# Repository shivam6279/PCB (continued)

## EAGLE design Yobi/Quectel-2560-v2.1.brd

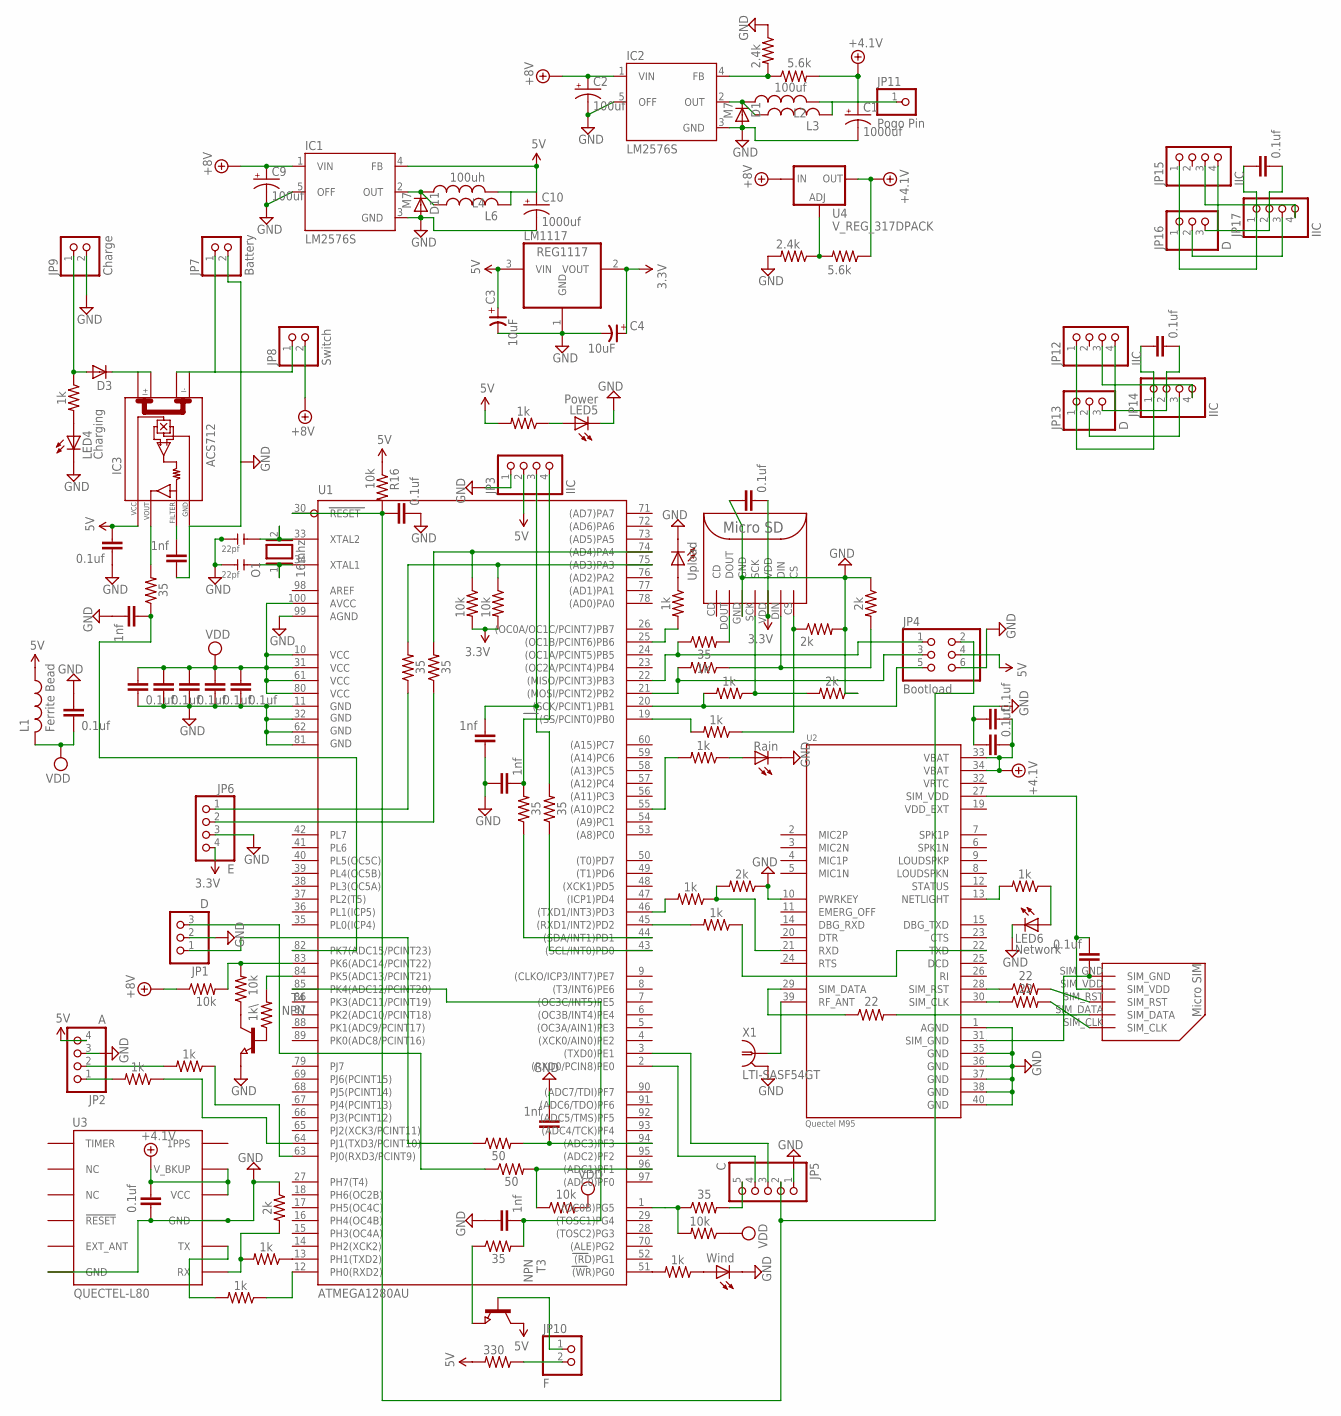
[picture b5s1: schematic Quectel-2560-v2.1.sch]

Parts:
C1, C10: 1000uf; 153CLV-1012
C2, C9: 100uf; CT7343
C3, C4: 10uF; 3528/T
C7, C8: 22pf; C0805
D1, D11: M7; SOD106A
D3: BYS10; SOD106A
DC1, DC2, DC3, DC4, DC5, DC6, DC7, DC8, DC9, DC10, DC11, DC15, DC16, DC18, DC19: 0.1uf; C0805
DC12, DC13, DC14, DC17, DC20, DC21: 1nf; C0805
IC1, IC2: LM2576S; TO263-5
IC3: ACS712; SO08
JP1, JP13, JP16: D; 1X03
JP2: A; 1X04
JP3, JP12, JP14, JP15, JP17: IIC; 1X04
JP4: Bootload; 2X03
JP5: C; 1X05
JP6: E; 1X04
JP7: Battery; 1X02
JP8: Switch; 1X02
JP9: Charge; 1X02
JP10: F; 1X02
JP11: Pogo Pin; 1X01
L1: Ferrite Bead; L2012C
L2: 100uf; PIS2816
L3, L6: L-US6000-XXX-RC; 6000-XXXX-RC
L4: 100uh; PIS2816
LED1: Rain; CHIP-LED0805
LED2: Upload; CHIP-LED0805
LED3: Wind; CHIP-LED0805
LED4: Charging; CHIP-LED0805
LED5: Power; CHIP-LED0805
LED6: Network; CHIP-LED0805
LM1117: REG1117; SOT223
O1: 16mhz; QS
R1, R5, R19, R22, R30, R35, R39, R42: 35; 0805
R4, R9, R23, R24, R29: 2k; 0805
R6, R7, R8, R12, R13, R14, R15, R17, R18, R25, R26, R27, R28, R32, R33: 1k; 0805
R10, R11, R47: 22; 0805
R16, R20, R34, R36, R40, R43, R44: 10k; 0805
R21, R31: 50; 0805
R41: 330; 0805
R45, R49: 2.4k; 0805
R46, R50: 5.6k; 0805
R48: 1k\; 0805
T3, T4: NPN; SOT23
U1: ATMEGA1280AU; TQFP100
U2: Quectel M95; XCVR_M95
U3: QUECTEL-L80
U4: V_REG_317DPACK; V-REG_DPACK
U$1: MICROSD
U$2: MICROSIM
X1: LTI-SASF54GT

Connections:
3.3V: C4.+, DC10.2, JP6.4, LM1117.2 (VOUT), R34.2, R36.2, U$1.VDD
5V: C3.+, C10.+, DC19.2, IC1.4 (FB), IC3.8 (VCC), JP2.4, JP3.2, JP4.4, L1.1, L4.2, L6.2, LM1117.3 (VIN), R16.1, R18.2, R41.2, T3.3 (C)
+4.1V: C1.+, DC6.2, DC7.2, DC16.1, JP11.1, L2.2, L3.2, R46.2, R50.1, U2.33 (VBAT), U2.34 (VBAT), U3.4 (VCC), U3.5 (V_BKUP), U4.4 (OUT)
+8V: C2.+, C9.+, IC1.1 (VIN), IC2.1 (VIN), JP8.2, R43.1, U4.3 (IN)
GND: C1.-, C2.-, C3.-, C4.-, C7.1, C8.1, C9.-, C10.-, D1.A, D11.A, DC1.2, DC2.2, DC3.2, DC4.2, DC5.2, DC6.1, DC7.1, DC10.1, DC11.2, DC12.1, DC13.1, DC14.1, DC16.2, DC17.2, DC18.1, DC19.1, DC20.1, DC21.2, IC1.3 (GND), IC1.5 (OFF), IC2.3 (GND), IC2.5 (OFF), IC3.5 (GND), JP1.2, JP2.3, JP3.1, JP4.6, JP5.1, JP6.3, JP7.2, JP9.2, LED1.C, LED2.C, LED3.C, LED4.C, LED5.C, LED6.C, LM1117.1 (GND), R4.1, R9.1, R23.2, R24.1, R29.1, R45.1, R49.2, T4.2 (E), U1.11 (GND), U1.32 (GND1), U1.62 (GND2), U1.81 (GND3), U1.99 (AGND), U2.1 (AGND), U2.10 (PWRKEY), U2.35 (GND), U2.36 (GND), U2.37 (GND), U2.38 (GND), U2.40 (GND), U3.3 (GND), U3.12 (GND), U$1.GND, X1.2, X1.3 (2), X1.4 (2), X1.5 (2)
unnamed: DC15.1, U2.31 (SIM_GND), U$2.SIM_GND
unnamed: DC15.2, U2.27 (SIM_VDD), U$2.SIM_VDD
unnamed: R10.1, U2.28 (SIM_RST)
unnamed: R11.1, U2.30 (SIM_CLK)
unnamed: DC8.1, JP12.1, JP13.1, JP14.1
unnamed: R10.2, U$2.SIM_RST
unnamed: LED2.A, R25.1
unnamed: JP5.4, U1.2 ((RXD0/PCIN8)PE0)
unnamed: JP5.3, U1.3 ((TXD0)PE1)
unnamed: R7.1, R24.2, U$1.SCK
unnamed: DC12.2, JP3.4, R5.2
unnamed: R6.1, R9.2, U$1.DIN
unnamed: DC11.1, JP4.2, JP5.2, R16.2, U1.30 (RESET)
unnamed: DC8.2, JP12.4, JP13.3, JP14.2
unnamed: JP13.2, JP14.3
unnamed: JP4.3, R6.2, U1.21 ((MOSI/PCINT2)PB2)
unnamed: JP4.5, R7.2, U1.20 ((SCK/PCINT1)PB1)
unnamed: DC21.1, R1.1, U1.82 (PK7(ADC15/PCINT23))
unnamed: IC3.4 (I-_1), JP7.1, JP8.1
unnamed: R8.2, U1.19 ((SS/PCINT0)PB0)
unnamed: U2.39 (RF_ANT), X1.1
unnamed: R22.2, R36.1, U1.75 ((AD3)PA3)
unnamed: R5.1, U1.44 ((SDA/INT1)PD1)
unnamed: D3.A, JP9.1, R26.1
unnamed: LED3.A, R28.1
unnamed: LED4.A, R26.2
unnamed: IC3.7 (VOUT), R1.2
unnamed: R11.2, U$2.SIM_CLK
unnamed: C7.2, O1.2, U1.33 (XTAL2)
unnamed: C8.2, O1.1, U1.34 (XTAL1)
unnamed: DC13.2, JP3.3, R30.2
unnamed: R28.2, U1.51 ((WR)PG0)
unnamed: LED1.A, R27.1
unnamed: R8.1, R23.1, U$1.CS
unnamed: R12.1, U1.13 (PH1(TXD2))
unnamed: R13.2, U3.2 (TX)
unnamed: R4.2, R12.2, U3.1 (RX)
unnamed: R25.2, U1.25 ((OC1B/PCINT6)PB6)
unnamed: R14.2, U1.46 ((TXD1/INT3)PD3)
unnamed: R15.2, U1.45 ((RXD1/INT2)PD2)
unnamed: R14.1, R29.2, U2.21 (RXD)
unnamed: R15.1, U2.22 (TXD)
unnamed: R19.2, R34.1, U1.74 ((AD4)PA4)
unnamed: JP5.5, R39.2
unnamed: JP12.3, JP14.4
unnamed: R20.1, R31.2, U1.96 ((ADC1)PF1)
unnamed: R27.2, U1.55 ((A10)PC2)
unnamed: JP4.1, R35.1, U1.22 ((MISO/PCINT3)PB3)
unnamed: R17.2, U2.13 (NETLIGHT)
unnamed: LED6.A, R17.1
unnamed: JP6.1, R22.1
unnamed: JP1.1, R21.1
unnamed: DC17.1, R21.2, U1.94 ((ADC3)PF3)
unnamed: R30.1, U1.43 ((SCL/INT0)PD0)
unnamed: JP6.2, R19.1
unnamed: JP1.3, R31.1
unnamed: JP2.2, R32.2
unnamed: LED5.A, R18.1
unnamed: JP10.2, R41.1
unnamed: R32.1, U1.63 (PJ0(RXD3/PCINT9))
unnamed: JP2.1, R33.2
unnamed: R35.2, U$1.DOUT
unnamed: D11.K, IC1.2 (OUT), L4.1, L6.1
unnamed: R33.1, U1.64 (PJ1(TXD3/PCINT10))
unnamed: R47.2, U$2.SIM_DATA
unnamed: R47.1, U2.29 (SIM_DATA)
unnamed: R49.1, R50.2, U4.1 (ADJ)
unnamed: R13.1, U1.12 (PH0(RXD2))
unnamed: R39.1, R40.2, U1.1 ((OC0B)PG5)
unnamed: DC9.1, JP15.1, JP16.1, JP17.1
unnamed: JP10.1, T3.1 (B)
unnamed: R42.1, T3.2 (E)
unnamed: DC14.2, R42.2, U1.85 (PK4(ADC12/PCINT20))
unnamed: R43.2, R44.2, U1.83 (PK6(ADC14/PCINT22))
unnamed: D1.K, IC2.2 (OUT), L2.1, L3.1
unnamed: IC2.4 (FB), R45.2, R46.1
unnamed: R44.1, T4.3 (C)
unnamed: R48.1, T4.1 (B)
unnamed: R48.2, U1.84 (PK5(ADC13/PCINT21))
unnamed: DC9.2, JP15.4, JP16.3, JP17.2
unnamed: JP15.3, JP17.4
unnamed: JP16.2, JP17.3
unnamed: D3.K, IC3.1 (I+_0)
unnamed: DC20.2, IC3.6 (FILTER)
VDD: DC1.1, DC2.1, DC3.1, DC4.1, DC5.1, DC18.2, L1.2, R20.2, R40.1, U1.10 (VCC), U1.31 (VCC1), U1.61 (VCC2), U1.80 (VCC3), U1.100 (AVCC)
VDD_EXT: U2.19 (VDD_EXT)
VRTC: U2.32 (VRTC)

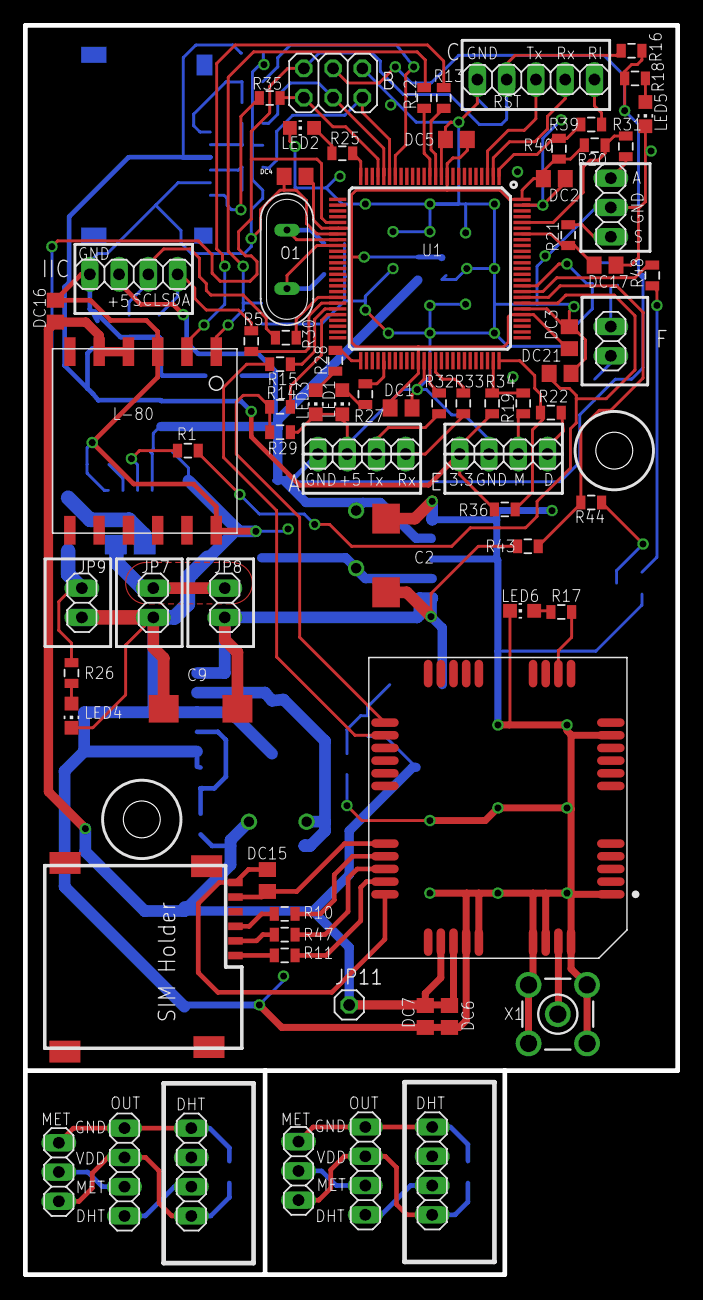
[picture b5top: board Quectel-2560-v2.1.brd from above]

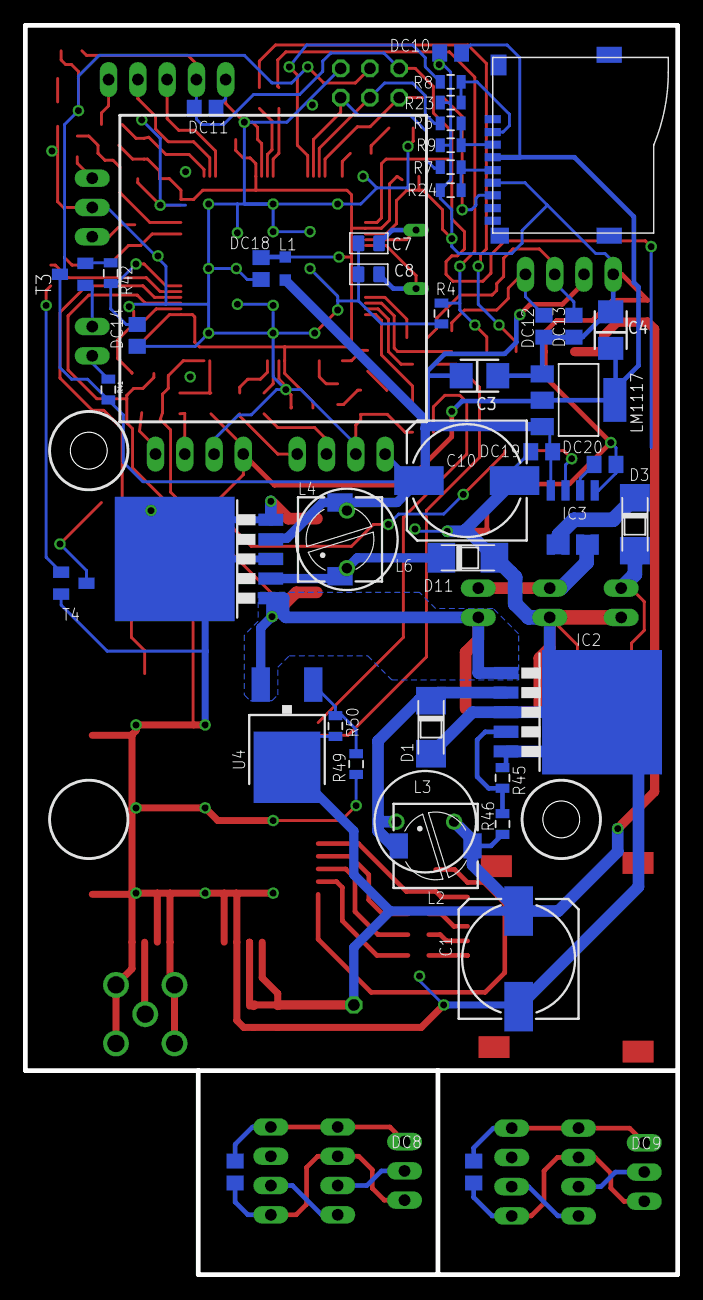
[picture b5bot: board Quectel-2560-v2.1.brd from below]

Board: 2 copper layers, 56.6 x 108.4 mm, 120 parts (45 on the bottom side), 90 nets.
